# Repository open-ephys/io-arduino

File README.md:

io-arduino
==========

Some applications require to generate (or read) digital channels on the host-PC running the GUI.
Most commonly, this is needed when closed-loop experiments make use of event detection on the host PC, for example with the phase-detector plugin.

The arduino i/o module for the GUI can interface with an aruino via the firmate firmware ( http://playground.arduino.cc/Interfacing/Firmata ) and assigns pins on the rduino to event channels in the software.
The module can generate up to 8 channels of digital I/O, where each channel can be assigned as input or output and assigned to an event channel in the GUI.

This shield plugs into any standard arduino board and provides convenient BNC connectors to the 8 input or output pins, as well as a connector to the standardized HDMI connector that is also used on the acquisition board.

See the wiki for more info: https://open-ephys.atlassian.net/wiki/pages/viewpage.action?pageId=16384044

For a similar, but much more powerful signal output device, check out the PulsePal (https://sites.google.com/site/pulsepalwiki/home) which also works seamlessly with the Open Ephys GUI.

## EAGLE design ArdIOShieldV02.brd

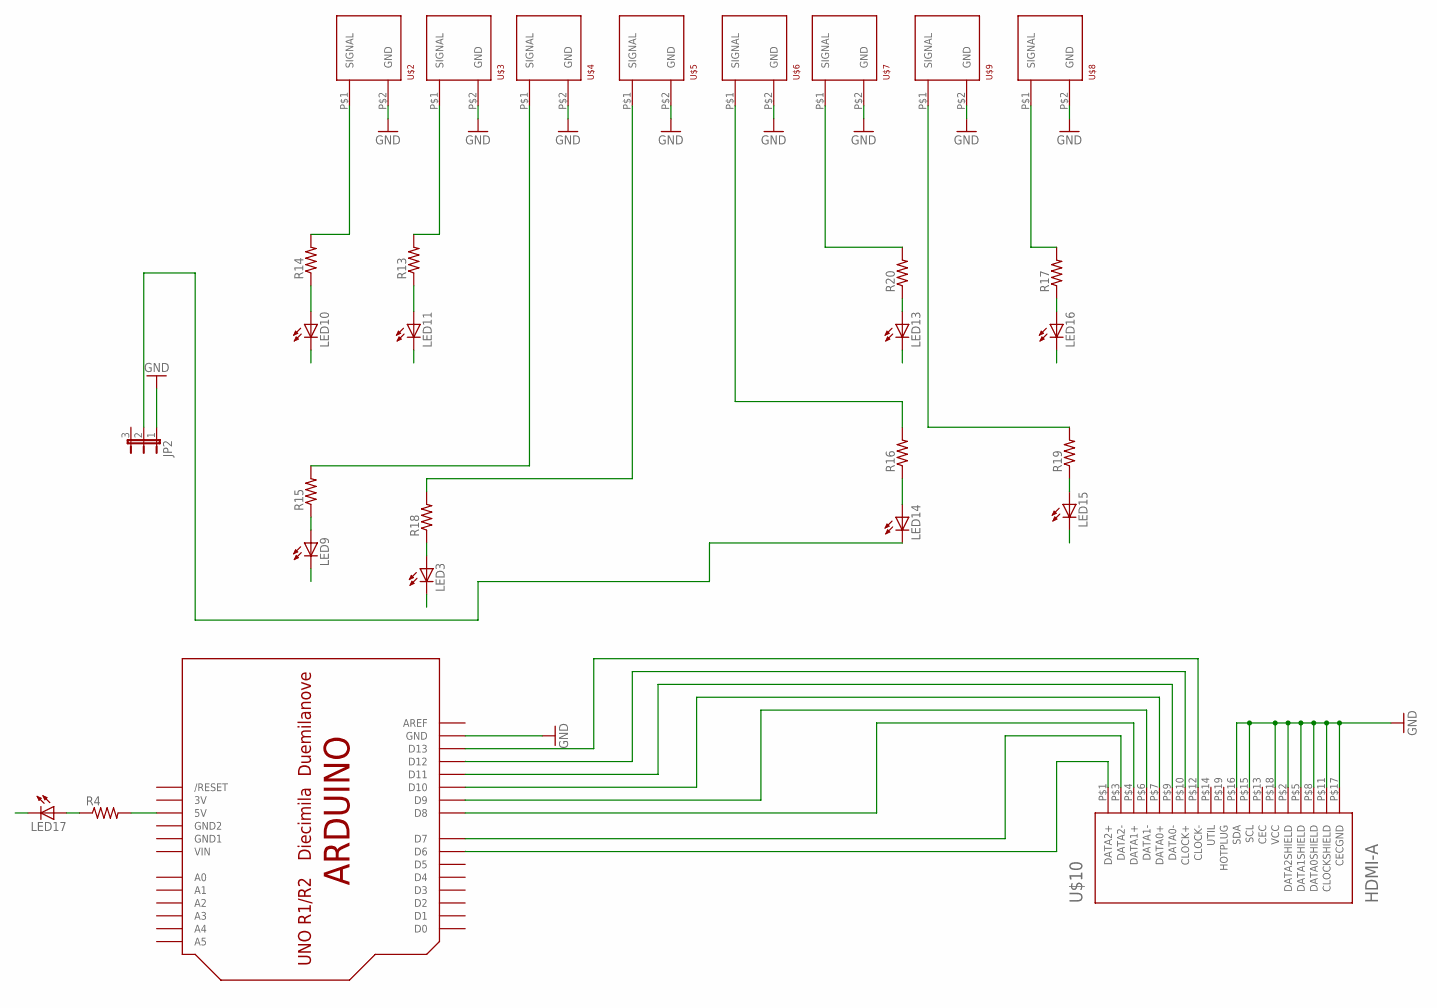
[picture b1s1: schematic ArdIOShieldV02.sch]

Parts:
JP2: JP2E; JP2
LED3, LED9, LED10, LED11, LED13, LED14, LED15, LED16, LED17: LEDCHIP-LED0805; CHIP-LED0805
R4, R13, R14, R15, R16, R17, R18, R19, R20: R_0603; 0603
U$1: ARDUINO-NOHOLE
U$2, U$3, U$4, U$5, U$6, U$7, U$8, U$9: BNC_VERTICAL
U$10: HDMI-A; HDMI_A

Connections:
3V: U$1.3V
D6: R17.2, U$1.D6, U$8.P$1 (SIGNAL), U$10.P$1 (DATA2+)
D7: R19.2, U$1.D7, U$9.P$1 (SIGNAL), U$10.P$3 (DATA2-)
D8: R20.2, U$1.D8, U$7.P$1 (SIGNAL), U$10.P$4 (DATA1+)
D9: R16.2, U$1.D9, U$6.P$1 (SIGNAL), U$10.P$6 (DATA1-)
D10: R18.2, U$1.D10, U$5.P$1 (SIGNAL), U$10.P$7 (DATA0+)
D11: R15.2, U$1.D11, U$4.P$1 (SIGNAL), U$10.P$9 (DATA0-)
D12: R13.2, U$1.D12, U$3.P$1 (SIGNAL), U$10.P$10 (CLOCK+)
D13: R14.2, U$1.D13, U$2.P$1 (SIGNAL), U$10.P$12 (CLOCK-)
GND: JP2.1, U$1.GND, U$2.P$2 (GND), U$3.P$2 (GND), U$4.P$2 (GND), U$5.P$2 (GND), U$6.P$2 (GND), U$7.P$2 (GND), U$8.P$2 (GND), U$9.P$2 (GND), U$10.P$2 (DATA2SHIELD), U$10.P$5 (DATA1SHIELD), U$10.P$8 (DATA0SHIELD), U$10.P$11 (CLOCKSHIELD), U$10.P$15 (SCL), U$10.P$16 (SDA), U$10.P$17 (CECGND), U$10.P$18 (VCC)
GND1: U$1.GND1
GND2: U$1.GND2
LED: JP2.2, LED3.C, LED9.C, LED10.C, LED11.C, LED13.C, LED14.C, LED15.C, LED16.C, LED17.C
unnamed: R4.2, U$1.5V
unnamed: LED17.A, R4.1
unnamed: LED10.A, R14.1
unnamed: LED11.A, R13.1
unnamed: LED9.A, R15.1
unnamed: LED3.A, R18.1
unnamed: LED14.A, R16.1
unnamed: LED15.A, R19.1
unnamed: LED13.A, R20.1
unnamed: LED16.A, R17.1
VIN: U$1.VIN

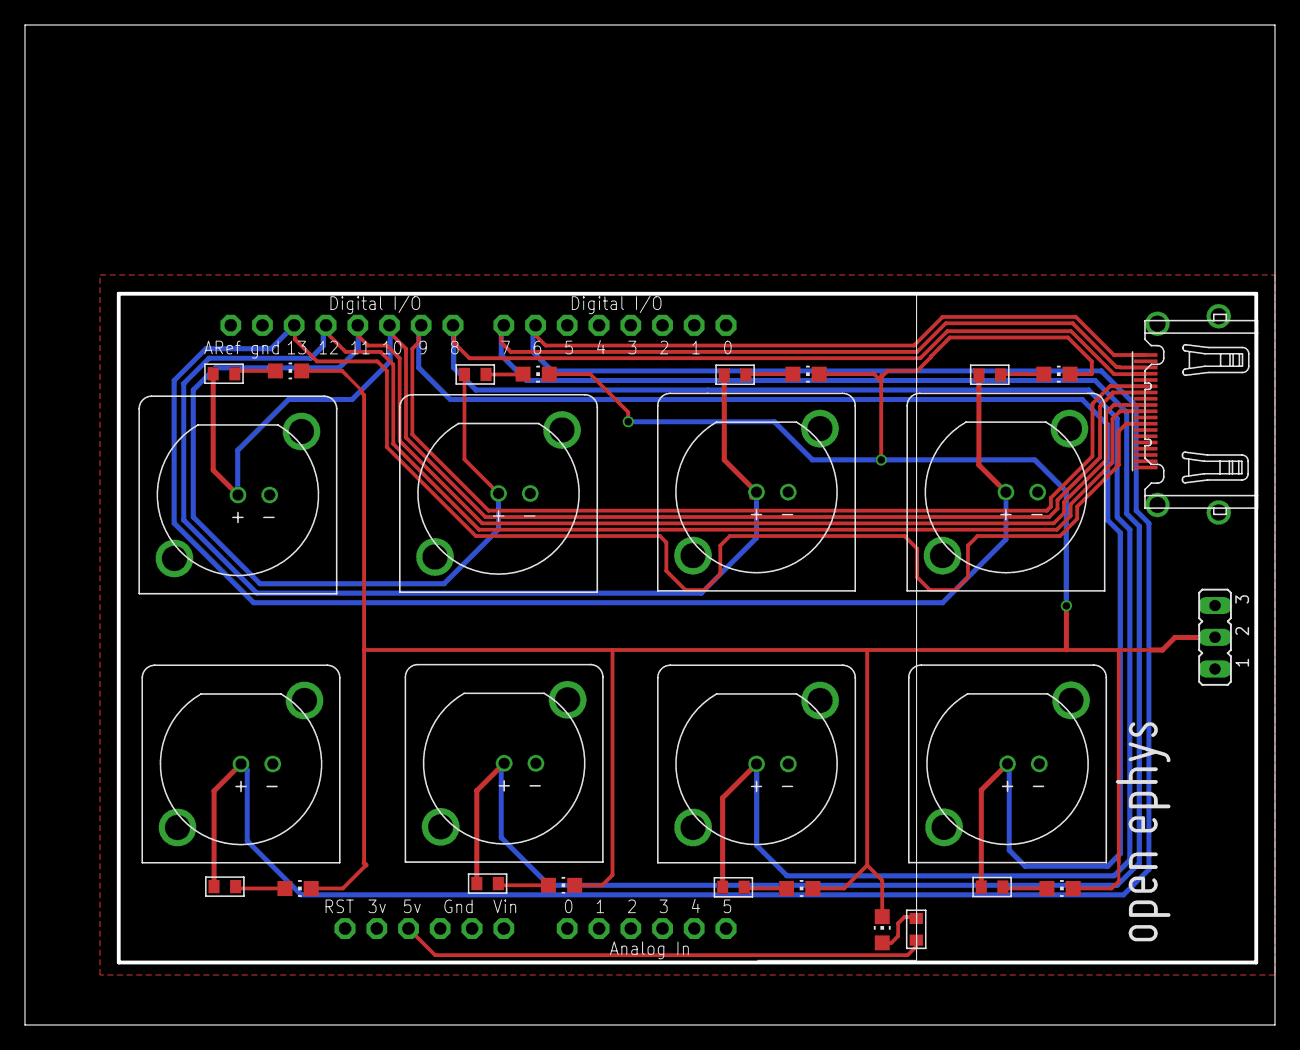
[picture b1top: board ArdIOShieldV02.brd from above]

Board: 2 copper layers, 100.0 x 80.0 mm, 30 parts (0 on the bottom side), 20 nets.

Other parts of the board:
U$11: OPEN_EPHYS_LOGO

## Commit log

2014-07-05 initial readme draft
2014-07-05 Eagle files for Arduino I/O Shield
    V01
2014-07-09 Update files for seeed processing
2014-08-14 clarified readme
2014-08-15 USB overlap fixed
    Shifted holes for arduino so board no longer rests on USB.
